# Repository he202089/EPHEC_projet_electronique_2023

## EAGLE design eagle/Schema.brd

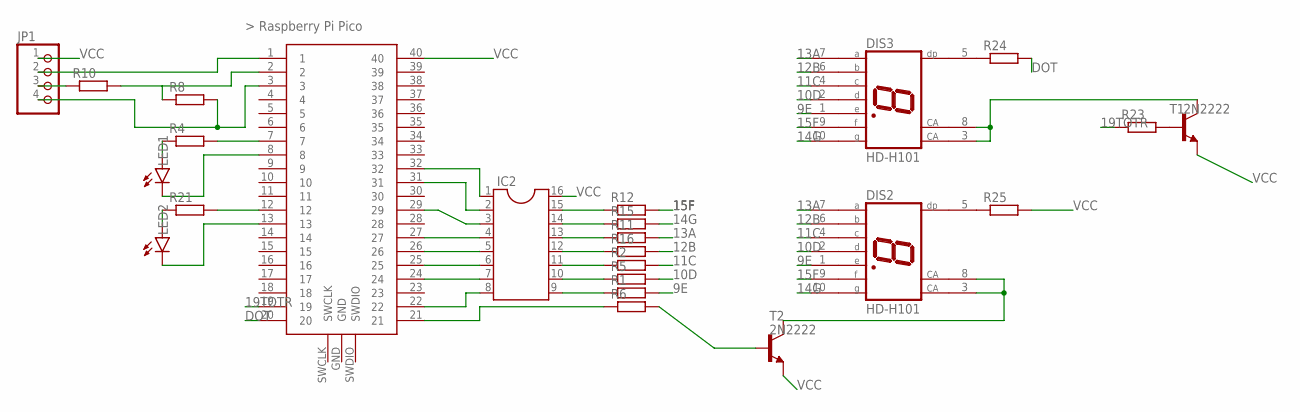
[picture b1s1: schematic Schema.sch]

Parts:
DIS2, DIS3: HD-H101; HDSP-M
IC2: DIL16
JP1: PINHD-1X4; 1X04
LED1, LED2: LED5MM
R1, R2, R4, R5, R6, R8, R10, R11, R12, R15, R16, R21, R23, R24, R25: R-EU_0207/10; 0207/10
T1, T2: 2N2222; TO18
U$1: RASPBERRY-PI-PICO_TH; FT_RASPBERRY-PI-PICO_TH

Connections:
9E: DIS2.1 (E), DIS3.1 (E), R1.2
10D: DIS2.2 (D), DIS3.2 (D), R5.2
11C: DIS2.4 (C), DIS3.4 (C), R2.2
12B: DIS2.6 (B), DIS3.6 (B), R16.2
13A: DIS2.7 (A), DIS3.7 (A), R11.2
14G: DIS2.10 (G), DIS3.10 (G), R15.2
15F: DIS2.9 (F), DIS3.9 (F), R12.2
19TOTR: R23.1, U$1.19
DOT: R24.2, U$1.20
unnamed: IC2.8, U$1.22
unnamed: JP1.4, R8.2, U$1.3
unnamed: R8.1, R10.2, U$1.2
unnamed: JP1.2, U$1.1
unnamed: JP1.3, R10.1
unnamed: R4.2, U$1.7
unnamed: LED1.A, R4.1
unnamed: LED1.K (C), U$1.8
unnamed: IC2.1, U$1.32
unnamed: IC2.2, U$1.31
unnamed: IC2.7, U$1.24
unnamed: IC2.6, U$1.25
unnamed: IC2.5, U$1.26
unnamed: IC2.4, U$1.27
unnamed: IC2.3, U$1.29
unnamed: IC2.15, R12.1
unnamed: IC2.14, R15.1
unnamed: R6.1, U$1.21
unnamed: IC2.13, R11.1
unnamed: IC2.12, R16.1
unnamed: IC2.11, R2.1
unnamed: IC2.10, R5.1
unnamed: IC2.9, R1.1
unnamed: R23.2, T1.2 (B)
unnamed: DIS3.3 (CA), DIS3.8 (CA), T1.3 (C)
unnamed: R21.2, U$1.12
unnamed: LED2.A, R21.1
unnamed: LED2.K (C), U$1.13
unnamed: DIS2.3 (CA), DIS2.8 (CA), T2.3 (C)
unnamed: R6.2, T2.2 (B)
unnamed: DIS2.5 (DP), R25.1
unnamed: DIS3.5 (DP), R24.1
VCC: IC2.16, JP1.1, R25.2, T1.1 (E), T2.1 (E), U$1.40

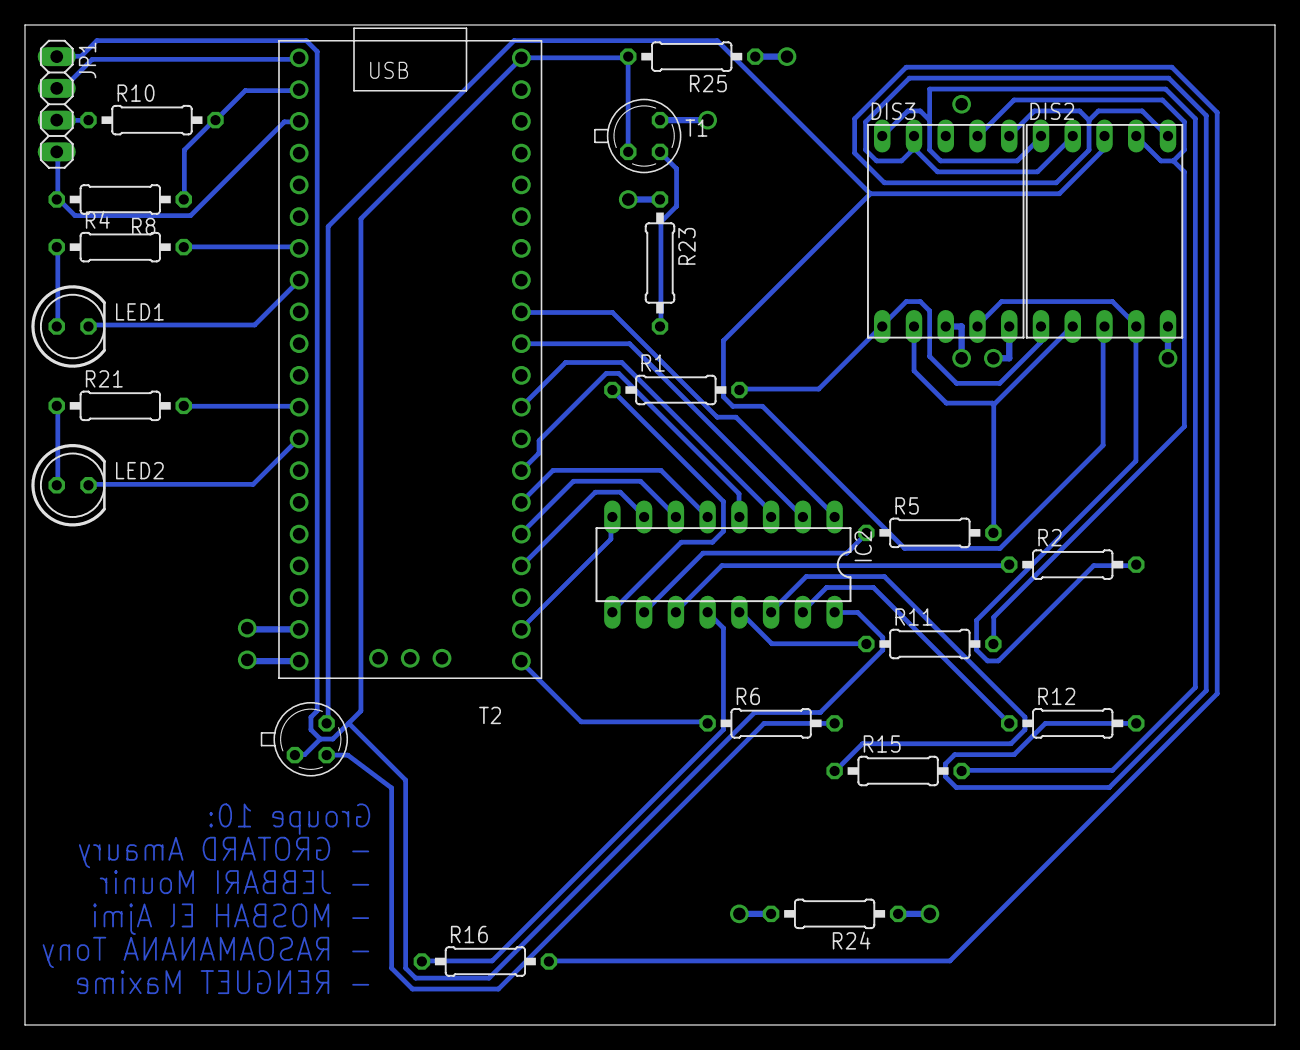
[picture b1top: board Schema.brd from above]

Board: 2 copper layers, 100.0 x 80.0 mm, 24 parts (0 on the bottom side), 42 nets.

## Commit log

2023-03-08 afternoon work
2023-03-08 Added a led
2023-03-09 [FIX] eagle schéma
2023-03-09 Change to Schema
2023-03-12 board file
2023-03-13 Améliorations
2023-03-13 [FIX] Transistor flipped
    Correction du prof
2023-05-10 pin_on
2023-05-12 [NEW] Code fonctionnel et rajout de code test
2023-05-12 [UPT] Clean up du code
2023-05-15 GUI Uniquement en lecture
2023-05-16 Update main.py
    Affichage de meilleurs messages
2023-05-17 removed useless files
